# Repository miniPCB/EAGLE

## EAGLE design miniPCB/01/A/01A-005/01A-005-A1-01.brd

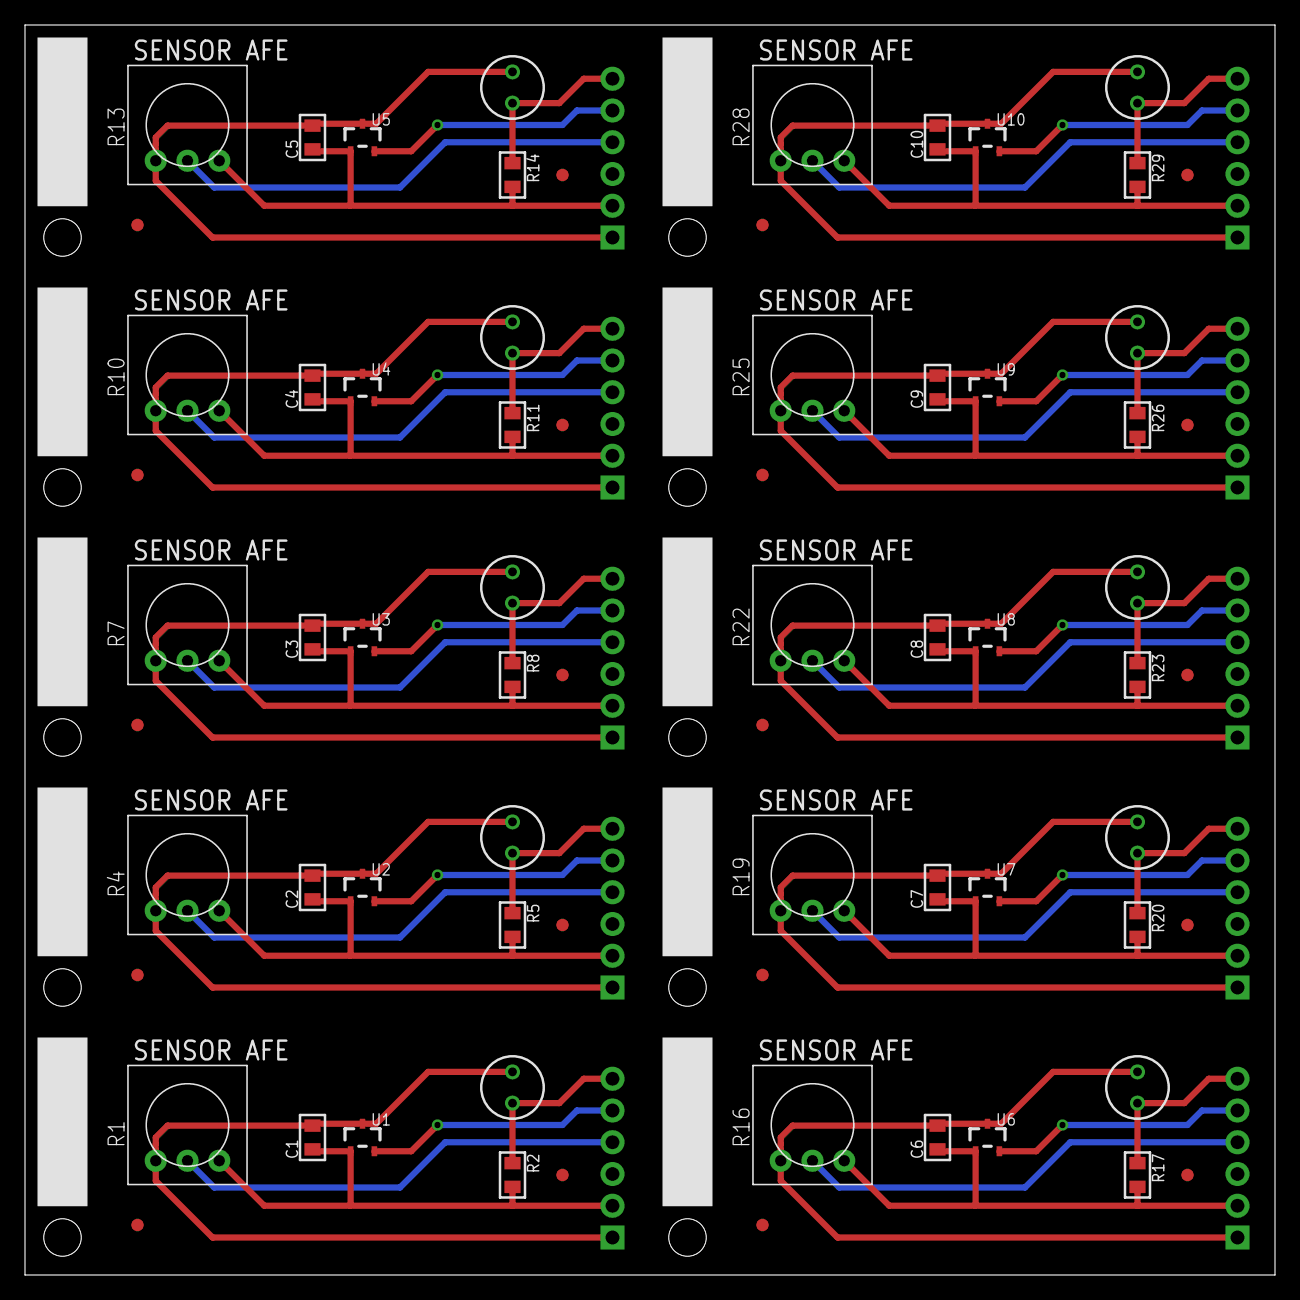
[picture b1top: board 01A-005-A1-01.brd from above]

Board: 2 copper layers, 100.0 x 100.0 mm, 90 parts (0 on the bottom side), 50 nets.

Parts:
C1, C2, C3, C4, C5, C6, C7, C8, C9, C10: C0805
P1, P2, P3, P4, P5, P6, P7, P8, P9, P10: PINS_6
PCB1, PCB2, PCB3, PCB4, PCB5, PCB6, PCB7, PCB8, PCB9, PCB10: MAIN CONNECTOR; MINIPCB_00A_20X50
R1, R4, R7, R10, R13, R16, R19, R22, R25, R28: 3386; TRIM-3386
R2, R5, R8, R11, R14, R17, R20, R23, R26, R29: R0805
R3, R6, R9, R12, R15, R18, R21, R24, R27, R30: NSL-5162; CERAMICPHOTOCELL
TP1, TP2, TP3, TP4, TP5, TP6, TP7, TP8, TP9, TP10, TP11, TP12, TP13, TP14, TP15, TP16, TP17, TP18, TP19, TP20: FIDUCIAL
U1, U2, U3, U4, U5, U6, U7, U8, U9, U10: MCP9700; SOT23

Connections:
GND: C1.2ASDF, P1.1, R1.1, R3.P$2, U1.3
GND1: C2.2ASDF, P2.1, R4.1, R6.P$2, U2.3
GND2: C3.2ASDF, P3.1, R7.1, R9.P$2, U3.3
GND3: C4.2ASDF, P4.1, R10.1, R12.P$2, U4.3
GND4: C5.2ASDF, P5.1, R13.1, R15.P$2, U5.3
GND5: C6.2ASDF, P6.1, R16.1, R18.P$2, U6.3
GND6: C7.2ASDF, P7.1, R19.1, R21.P$2, U7.3
GND7: C8.2ASDF, P8.1, R22.1, R24.P$2, U8.3
GND8: C9.2ASDF, P9.1, R25.1, R27.P$2, U9.3
GND9: C10.2ASDF, P10.1, R28.1, R30.P$2, U10.3
unnamed: P1.5, U1.2
unnamed: P1.4, R1.2
unnamed: P1.6, R2.1, R3.P$1
unnamed: P2.5, U2.2
unnamed: P2.4, R4.2
unnamed: P2.6, R5.1, R6.P$1
unnamed: P3.5, U3.2
unnamed: P3.4, R7.2
unnamed: P3.6, R8.1, R9.P$1
unnamed: P4.5, U4.2
unnamed: P4.4, R10.2
unnamed: P4.6, R11.1, R12.P$1
unnamed: P5.5, U5.2
unnamed: P5.4, R13.2
unnamed: P5.6, R14.1, R15.P$1
unnamed: P6.5, U6.2
unnamed: P6.4, R16.2
unnamed: P6.6, R17.1, R18.P$1
unnamed: P7.5, U7.2
unnamed: P7.4, R19.2
unnamed: P7.6, R20.1, R21.P$1
unnamed: P8.5, U8.2
unnamed: P8.4, R22.2
unnamed: P8.6, R23.1, R24.P$1
unnamed: P9.5, U9.2
unnamed: P9.4, R25.2
unnamed: P9.6, R26.1, R27.P$1
unnamed: P10.5, U10.2
unnamed: P10.4, R28.2
unnamed: P10.6, R29.1, R30.P$1
V+: C1.1ASD, P1.2, R1.3, R2.2, U1.1
V+1: C2.1ASD, P2.2, R4.3, R5.2, U2.1
V+2: C3.1ASD, P3.2, R7.3, R8.2, U3.1
V+3: C4.1ASD, P4.2, R10.3, R11.2, U4.1
V+4: C5.1ASD, P5.2, R13.3, R14.2, U5.1
V+5: C6.1ASD, P6.2, R16.3, R17.2, U6.1
V+6: C7.1ASD, P7.2, R19.3, R20.2, U7.1
V+7: C8.1ASD, P8.2, R22.3, R23.2, U8.1
V+8: C9.1ASD, P9.2, R25.3, R26.2, U9.1
V+9: C10.1ASD, P10.2, R28.3, R29.2, U10.1

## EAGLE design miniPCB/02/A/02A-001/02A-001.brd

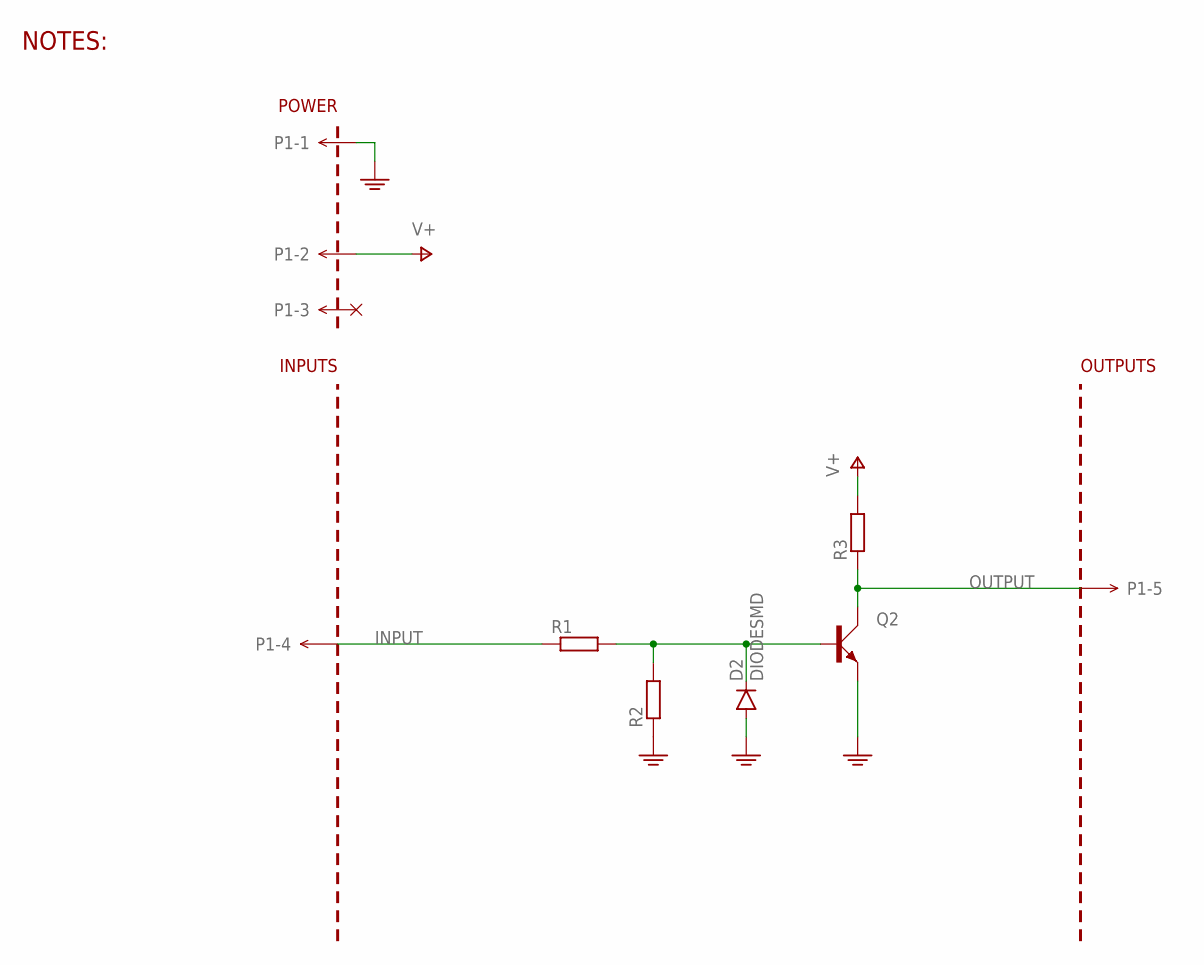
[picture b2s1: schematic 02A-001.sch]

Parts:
D2: DIODESMD; DO214AC
P1: MINIPCB_5P5P; PINS_1X5
PCB1: MINIPCB_0P00A-20X25; MINIPCB_00A_20X25; PART_NUMBER 02A-001
Q2: BJT_NPNBEC; SOT23
R1, R2, R3: RESISTORSMD; R0805

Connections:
GND: D2.A, P1.1, Q2.2 (E), R2.1
INPUT: P1.4, R1.1
OUTPUT: P1.5, Q2.3 (C), R3.1
PROTECTED_INPUT: D2.C, Q2.1 (B), R1.2, R2.2
V+: P1.2, R3.2

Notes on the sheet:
NOTES:

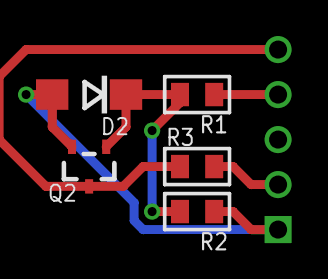
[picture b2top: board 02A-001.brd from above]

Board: 2 copper layers, 7 parts (0 on the bottom side), 5 nets.

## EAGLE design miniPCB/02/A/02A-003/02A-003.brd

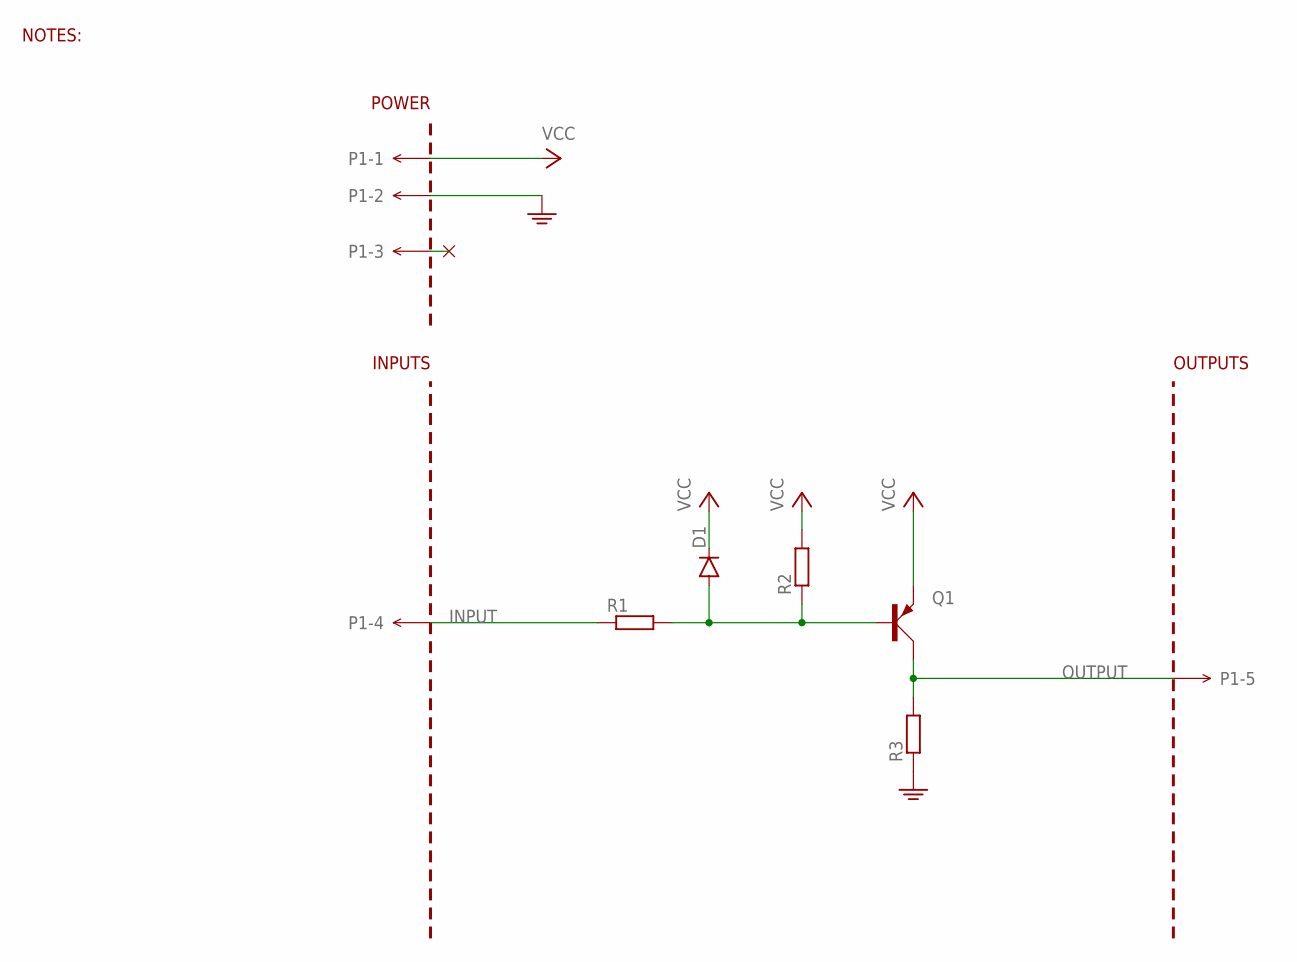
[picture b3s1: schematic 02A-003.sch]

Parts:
D1: DIODESMD; DO214AC
P1: MINIPCB_5P5P; PINS_1X5
PCB1: MINIPCB_0P00A-20X25; MINIPCB_00A_20X25; PART_NUMBER 02A-003
Q1: BJT_PNPBEC; SOT23
R1, R2, R3: RESISTORSMD; R0805

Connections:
GND: P1.2, R3.1
INPUT: P1.4, R1.1
OUTPUT: P1.5, Q1.3 (C), R3.2
PROTECTED_INPUT: D1.A, Q1.1 (B), R1.2, R2.1
VCC: D1.C, P1.1, Q1.2 (E), R2.2

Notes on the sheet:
NOTES:

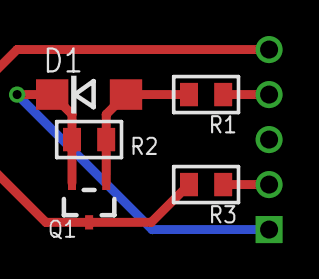
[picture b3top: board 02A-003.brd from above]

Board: 2 copper layers, 7 parts (0 on the bottom side), 5 nets.

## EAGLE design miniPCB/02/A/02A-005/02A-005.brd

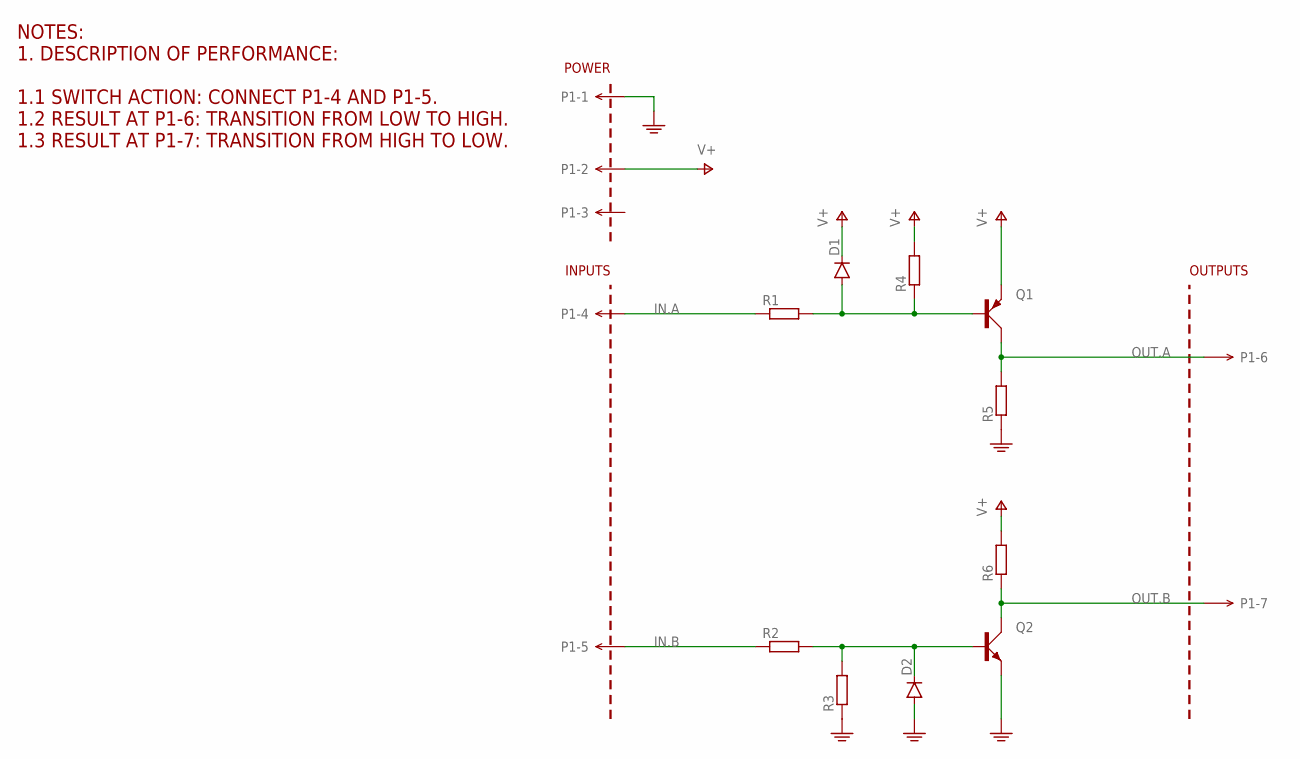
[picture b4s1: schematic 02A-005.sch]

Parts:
D1, D2: DIODESMD; DO214AC
P1: MINIPCB_7P; PINS_1X7
PCB1: MINIPCB_0P00A-20X25; MINIPCB_00A_20X25; PART_NUMBER 02A-005
Q1: BJT_PNPBEC; SOT23
Q2: BJT_NPNBEC; SOT23
R1, R2, R3, R4, R5, R6: RESISTORSMD; R0805

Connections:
GND: D2.A, P1.1, Q2.2 (E), R3.1, R5.1
IN.A: P1.4, R1.1
IN.A.PROTECTED: D1.A, Q1.1 (B), R1.2, R4.1
IN.B: P1.5, R2.1
IN.B.PROTECTED: D2.C, Q2.1 (B), R2.2, R3.2
OUT.A: P1.6, Q1.3 (C), R5.2
OUT.B: P1.7, Q2.3 (C), R6.1
V+: D1.C, P1.2, Q1.2 (E), R4.2, R6.2

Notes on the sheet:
NOTES: 1. DESCRIPTION OF PERFORMANCE: 1.1 SWITCH ACTION: CONNECT P1-4 AND P1-5. 1.2 RESULT AT P1-6: TRANSITION FROM LOW TO HIGH. 1.3 RESULT AT P1-7: TRANSITION FROM HIGH TO LOW.

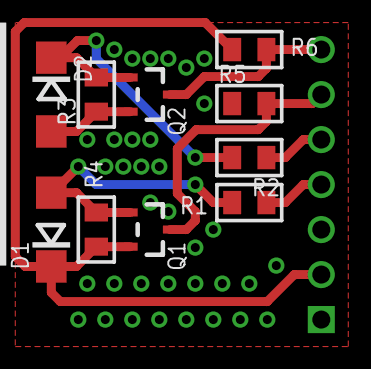
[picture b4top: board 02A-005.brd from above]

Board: 2 copper layers, 12 parts (0 on the bottom side), 8 nets.

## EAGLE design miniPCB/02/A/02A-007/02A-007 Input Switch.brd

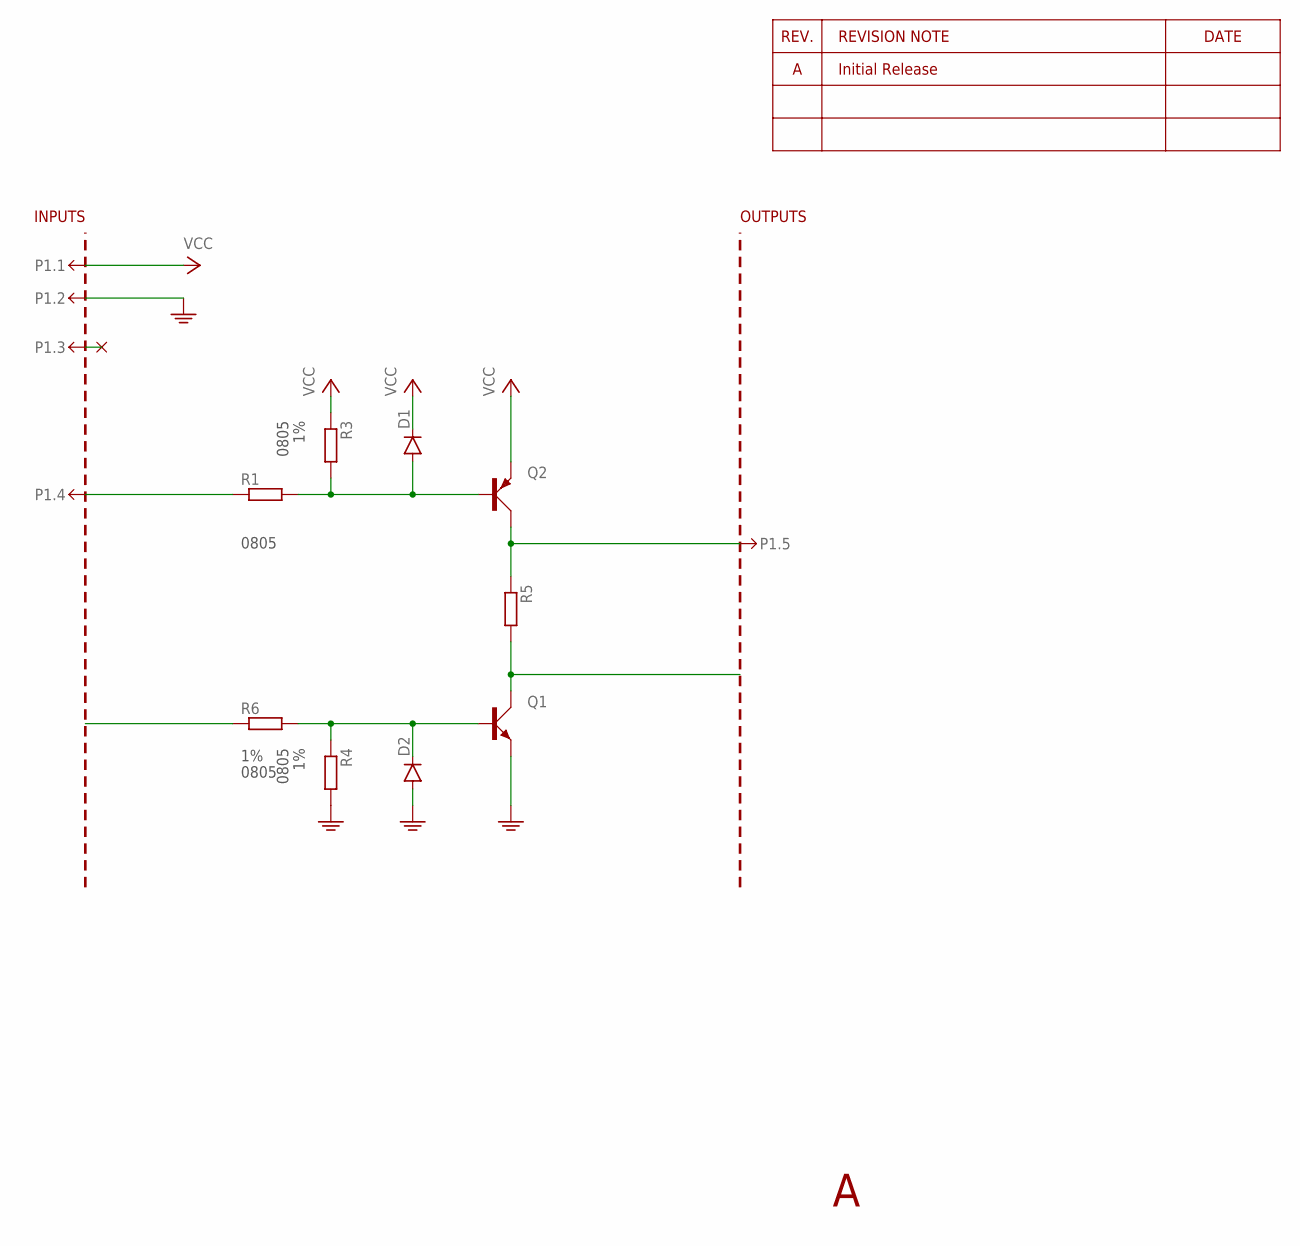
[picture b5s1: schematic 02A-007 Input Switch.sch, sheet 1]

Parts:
D1, D2: DIODE-SOD80C; SOD80C
P1.: MINIPCB_4INCH; PCB_5
Q1: BJT_NPNBEC; SOT23; MFG_PN 2N3904
Q2: BJT_PNPBEC; SOT23; MFG_PN 2N3906
R1, R4, R6: R-EU_1%_R0805; R0805; TOLERANCE 1%
R3: R-EU_1%_R0805; R0805
R5: R-EU__R0805; R0805

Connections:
GND: D2.A, P1..1, Q1.2 (E), R4.2
INPUT: P1..4, R1.1
unnamed: D1.A, Q2.1 (B), R1.2, R3.2
unnamed: Q1.3 (C), R5.2
unnamed: D2.C, Q1.1 (B), R4.1, R6.2
unnamed: P1..5, Q2.3 (C), R5.1
VCC: D1.C, P1..2, Q2.2 (E), R3.1

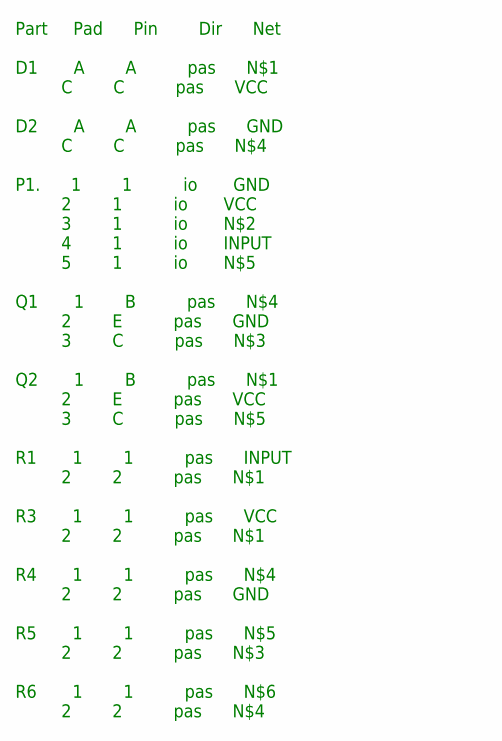
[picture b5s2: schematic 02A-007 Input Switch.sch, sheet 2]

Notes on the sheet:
Part Pad Pin Dir Net D1 A A pas N$1 C C pas VCC D2 A A pas GND C C pas N$4 P1. 1 1 io GND 2 1 io VCC 3 1 io N$2 4 1 io INPUT 5 1 io N$5 Q1 1 B pas N$4 2 E pas GND 3 C pas N$3 Q2 1 B pas N$1 2 E pas VCC 3 C pas N$5 R1 1 1 pas INPUT 2 2 pas N$1 R3 1 1 pas VCC 2 2 pas N$1 R4 1 1 pas N$4 2 2 pas GND R5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

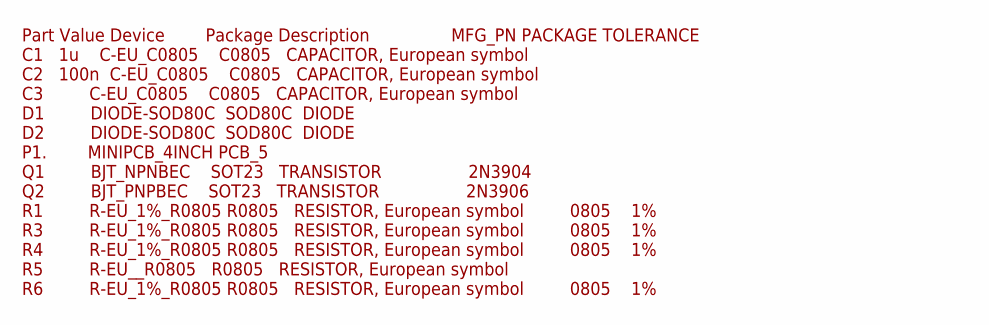
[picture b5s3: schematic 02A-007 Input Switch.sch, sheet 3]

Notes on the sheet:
Part Value Device Package Description MFG_PN PACKAGE TOLERANCE C1 1u C-EU_C0805 C0805 CAPACITOR, European symbol C2 100n C-EU_C0805 C0805 CAPACITOR, European symbol C3 C-EU_C0805 C0805 CAPACITOR, European symbol D1 DIODE-SOD80C SOD80C DIODE D2 DIODE-SOD80C SOD80C DIODE P1. MINIPCB_4INCH PCB_5 Q1 BJ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

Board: 2 copper layers, 10 parts (0 on the bottom side), 7 nets, no tracks yet.

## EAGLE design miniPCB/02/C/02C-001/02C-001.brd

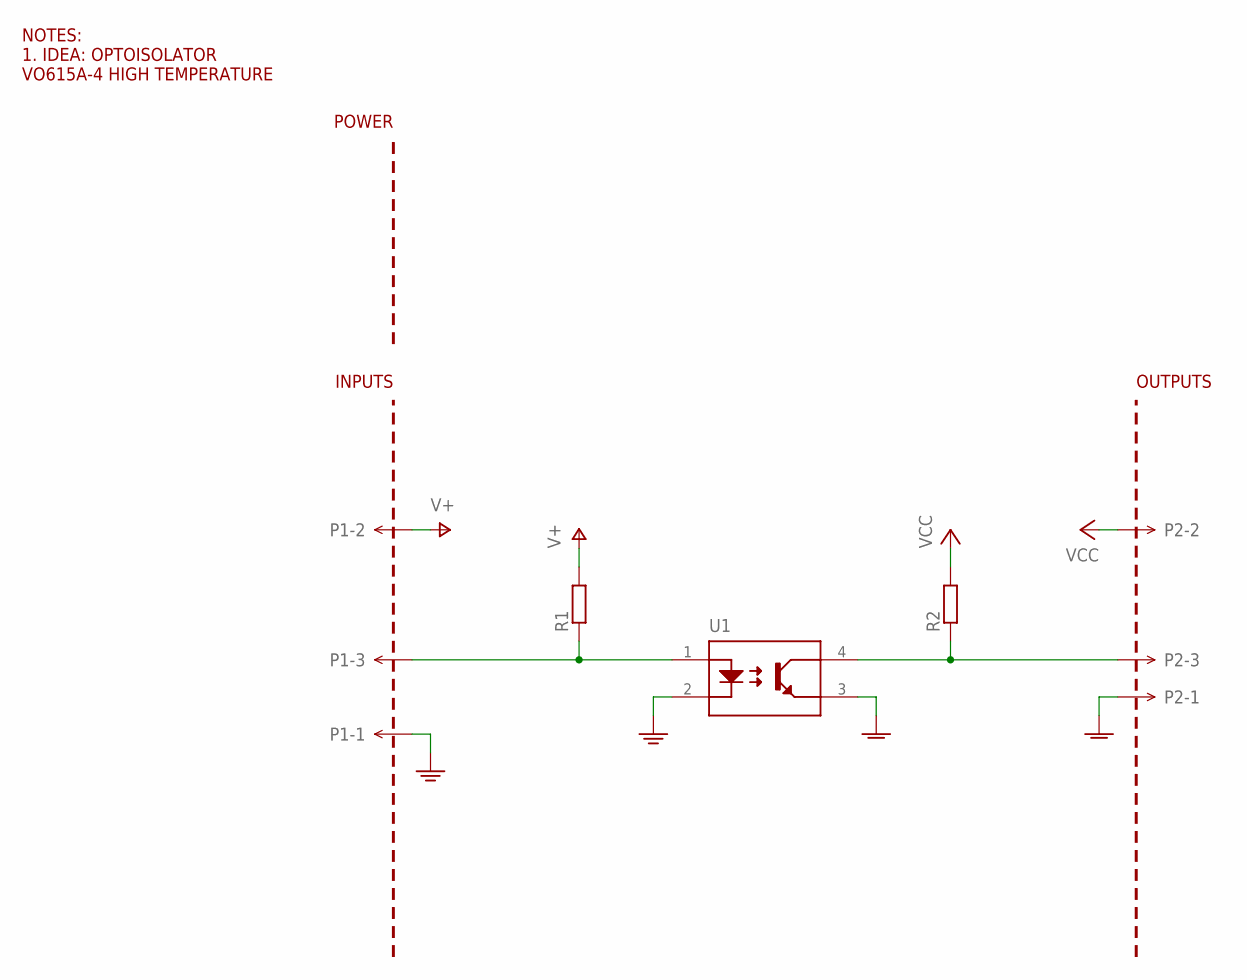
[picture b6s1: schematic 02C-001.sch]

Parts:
P1, P2: MINIPCB_3P; PINS_3
PCB1: MINIPCB_0P00A-20X25; MINIPCB_00A_20X25; PART_NUMBER 02C-001
R1, R2: RESISTORSMD; R0805
U1: OPTOCOUPLER8MM; OPTOCOUPLE

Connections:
GND: P1.1, U1.2
GNDA: P2.1, U1.3
unnamed: P1.3, R1.1, U1.1
unnamed: P2.3, R2.1, U1.4
V+: P1.2, R1.2
VCC: P2.2, R2.2

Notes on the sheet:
NOTES: 1. IDEA: OPTOISOLATOR VO615A-4 HIGH TEMPERATURE

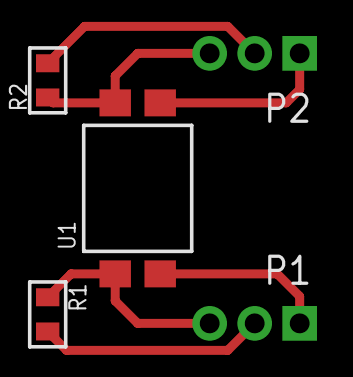
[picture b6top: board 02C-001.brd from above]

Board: 2 copper layers, 6 parts (0 on the bottom side), 6 nets.
